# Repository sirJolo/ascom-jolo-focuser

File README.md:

ver 2.2 
==================
 - Driver local cache
 - Other fixes

ver 2.0 production
==================
 - EXT connector extended 
 - PCB redesigned a little and fixed
 - encoder support removed from Arduino sketch
 - 'Connection timeout for message #' bug fixed

ver 1.5 production
==================
Changelog:
 - encoder support removed
 - PWM stepper duty cycle control switched to Arduino native
 - Eagle project for PCB and reference schematic added (for fixed version wait for 1.6)
 - Reference solution uses L298 stepper driver and some of Arduino pins are now externally available for additional options. Driver implementation will be in 2.0

ver 1.4
==================
Changelog:
 - max focuser position now is 1,000,000
 - driver backslash control removed - noone uses it
 - buzzer turned off by default, can be turned on with BUZZER_ON flag
 - stepper now controlled with half step by default. Please change stepper speed (200%) and step size (50%) in driver settings
 - manual control now with two buttons that perform accelerated motion. Buttons connected to ENCODER_A_PIN and ENCODER_B_PIN
 - MANUAL_FOCUS_MODE added, default to 1 - control with button, NOT encoder
 - STEPPER_ACC increased to 2500
 - MANUAL_STEPPER_ACC for manual button control. Default is 600
 - STEPPER_PWM_FREQ changed to 1000Hz

ascom-jolo-focuser
==================
ASCOM absolute focuser developed using Arduino Nano board and Visual Studio 2008 for ASCOM driver. Uses DS1820 temperature sensor for temperature focus compensation and rotary encoder for manual focus change. Buzzer can be connected to indicate some user interactions, so there is no need to pay attention on any blinking LEDs. Communication with PC is performed over USB cable using Arduino Nano built in UART converter. RS commands set was chosen to implement ASCOM IFocus2 interface with minimum effort, so it is not compatibile with other focuser standards (like Robofocus) that have too much RS communication overhead.
Compiled microcontroller code is 18KB large, so it will not fit into boards with 16KB chip (like Arduino Nano version lower than 3.0). Code size can be shrinked by eliminating 3rd party libraries and making custom implementations.

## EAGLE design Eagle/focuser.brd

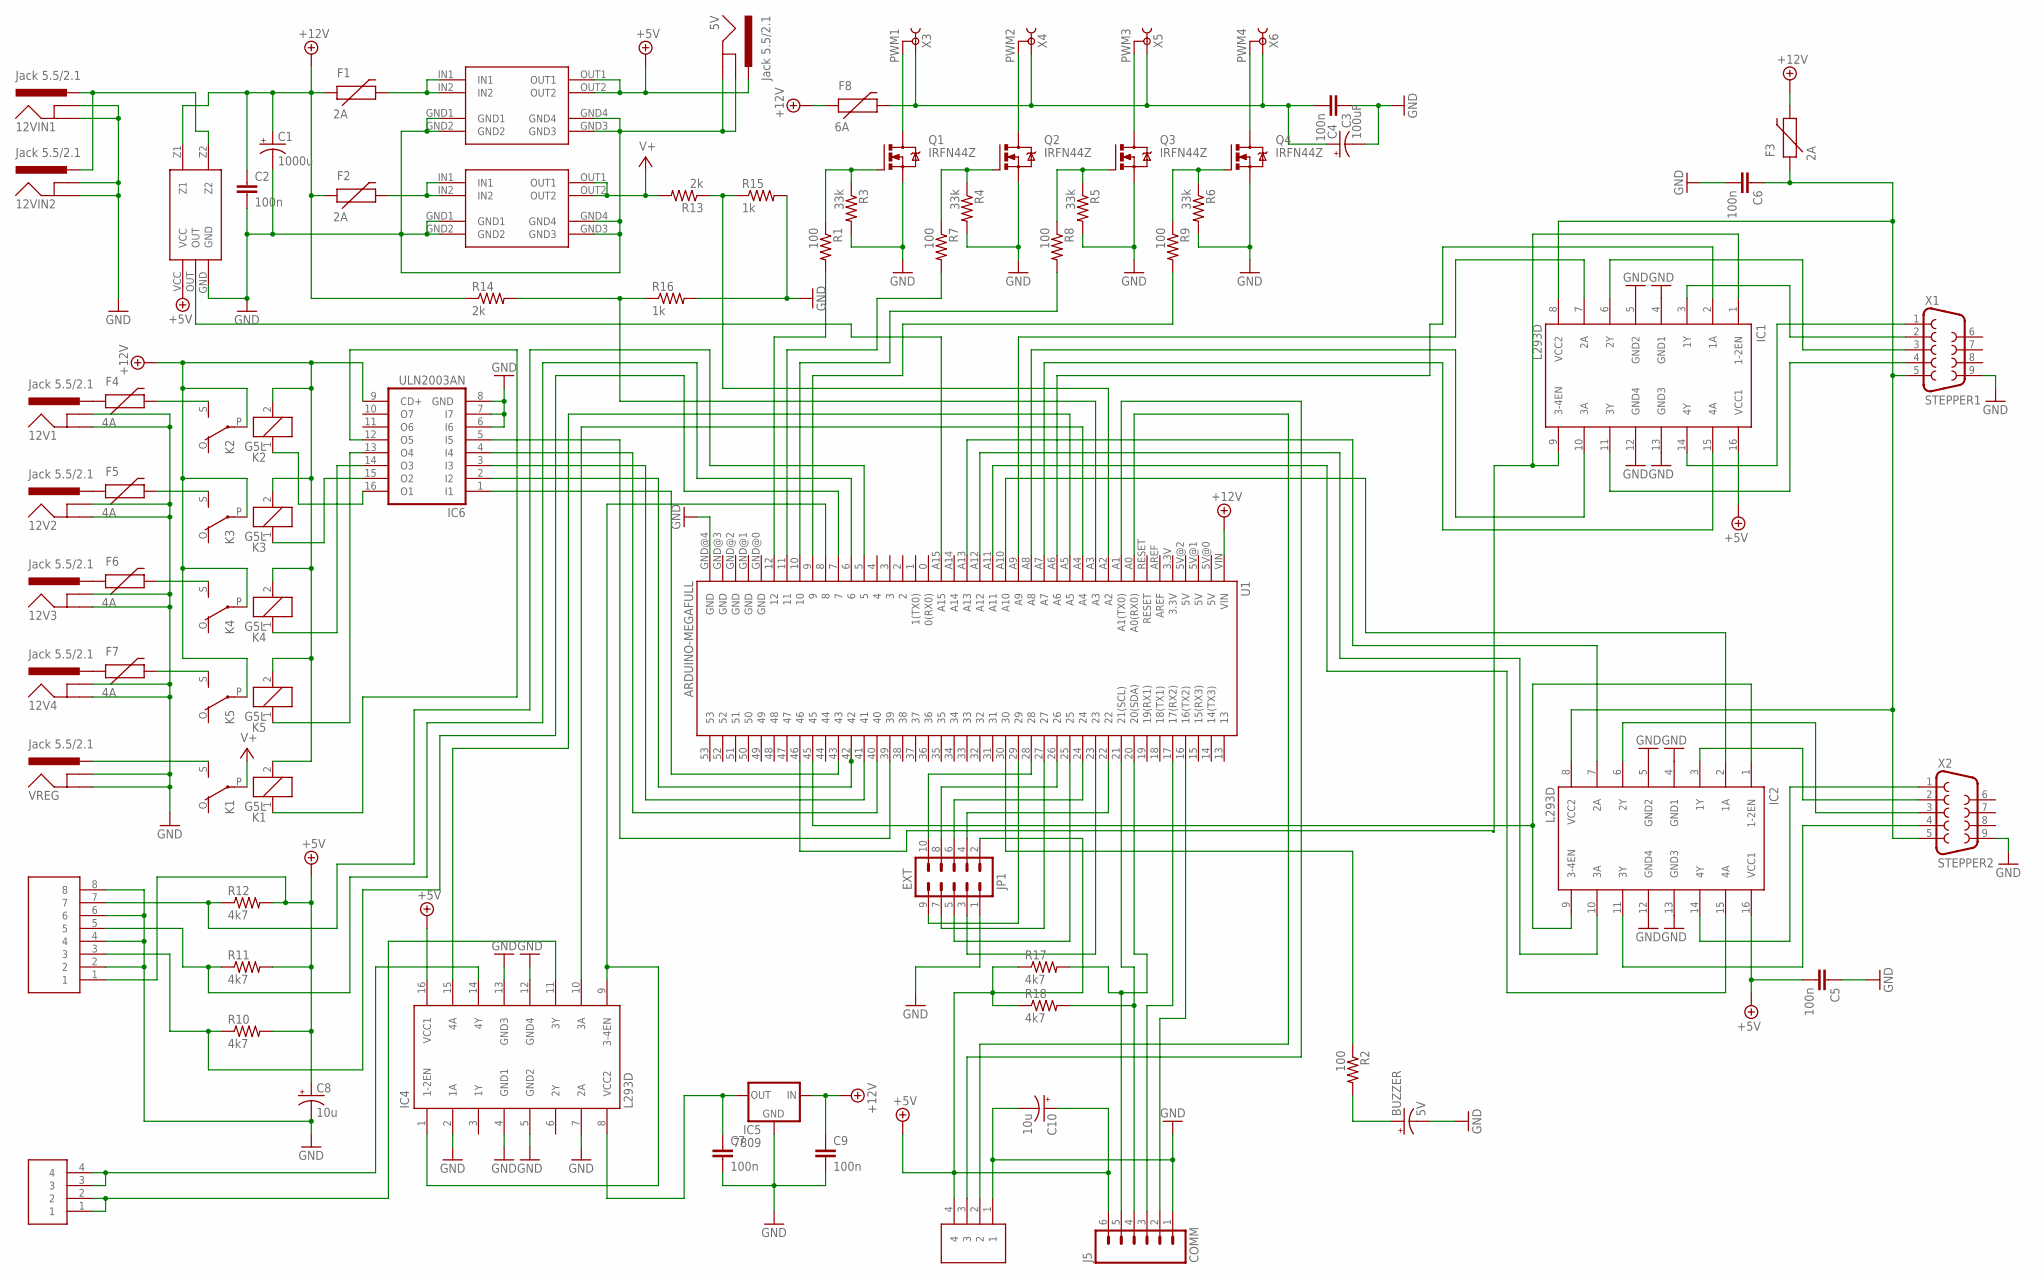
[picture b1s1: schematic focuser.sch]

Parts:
5V, 12V1, 12V2, 12V3, 12V4, 12VIN1, 12VIN2: Jack 5.5/2.1; POWER_JACK_PTH
BUZZER: 5V; CPOL-RADIAL-1000UF-25V
C1: 1000u; CPOL-RADIAL-1000UF-25V
C2, C3, C5, C6, C7, C9: 100n; CAP-PTH-5MM
C4: 100uF; CPOL-RADIAL-100UF-25V
C8, C10: 10u; CPOL-RADIAL-10UF-25V
F1, F2, F3: 2A; PTC
F4, F5, F6, F7: 4A; PTC
F8: 6A; PTC
IC1: L293D; DIL16
IC2, IC4: L293D; DIL16; MPN L293D
IC5: 7809; TO220-IGO
IC6: ULN2003AN; DIL16
J5: COMM; RJ11-6
JP1: EXT; AVR_ICSP
K1, K2, K3, K4, K5: G5L; G5LE
Q1, Q2, Q3, Q4: IRFN44Z; TO220BV
R1, R2, R7, R8, R9: 100; AXIAL-0.3
R3, R4, R5, R6: 33k; AXIAL-0.3
R10, R11, R12, R17, R18: 4k7; AXIAL-0.3
R13, R14: 2k; AXIAL-0.3
R15, R16: 1k; AXIAL-0.3
U1: ARDUINO-MEGAFULL; ARDUINO_MEGA
U$1, U$2: MP1584-BUCK; DCDC-1584
U$3: ASC712
U$4, U$5: RJ9
U$8: RJ45
VREG: Jack 5.5/2.1; POWER_JACK_PTH
X1: STEPPER1; DB9
X2: STEPPER2; DB9
X3: PWM1; TOBU3
X4: PWM2; TOBU3
X5: PWM3; TOBU3
X6: PWM4; TOBU3

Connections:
+5V: 5V.PWR, C5.2, C8.1 (+), C10.1 (+), IC1.16 (VCC1), IC2.16 (VCC1), IC4.16 (VCC1), J5.6, JP1.2, R10.P$2 (2), R11.P$2 (2), R12.P$2 (2), R17.P$1 (1), R18.P$1 (1), U$1.OUT1, U$1.OUT2, U$3.VCC, U$5.4, U$8.1
+12V: C1.1 (+), C2.1, C9.1, F1.P$1 (1), F2.P$1 (1), F3.P$2 (2), F8.P$1 (1), IC5.IN, IC6.9 (CD+), K1.2, K2.2, K2.P, K3.2, K3.P, K4.2, K4.P, K5.2, K5.P, R14.P$1 (1), U1.VIN, U$3.Z1
GND: 5V.GND, 5V.GNDBREAK, 12V1.GND, 12V1.GNDBREAK, 12V2.GND, 12V2.GNDBREAK, 12V3.GND, 12V3.GNDBREAK, 12V4.GND, 12V4.GNDBREAK, 12VIN1.GND, 12VIN1.GNDBREAK, 12VIN2.GND, 12VIN2.GNDBREAK, BUZZER.2 (-), C1.2 (-), C2.2, C3.1, C4.2 (-), C5.1, C6.2, C7.2, C8.2 (-), C9.2, C10.2 (-), IC1.4 (GND1), IC1.5 (GND2), IC1.12 (GND4), IC1.13 (GND3), IC2.4 (GND1), IC2.5 (GND2), IC2.12 (GND4), IC2.13 (GND3), IC4.2 (1A), IC4.4 (GND1), IC4.5 (GND2), IC4.7 (2A), IC4.12 (GND4), IC4.13 (GND3), IC5.GND, IC6.6 (I6), IC6.7 (I7), IC6.8 (GND), J5.1, JP1.1, Q1.S, Q2.S, Q3.S, Q4.S, R3.P$2 (2), R4.P$2 (2), R5.P$2 (2), R6.P$2 (2), R15.P$2 (2), R16.P$2 (2), U1.GND@4 (GND), U$1.GND1, U$1.GND2, U$1.GND3, U$1.GND4, U$2.GND1, U$2.GND2, U$2.GND3, U$2.GND4, U$3.GND, U$5.1, U$8.2, U$8.4, U$8.6, U$8.8, VREG.GND, VREG.GNDBREAK, X1.9, X2.9
unnamed: J5.4, R18.P$2 (2), U1.21 (21(SCL))
unnamed: J5.5, R17.P$2 (2), U1.20 (20(SDA))
unnamed: C7.1, IC4.8 (VCC2), IC5.OUT
unnamed: IC2.14 (4Y), X2.1
unnamed: IC1.3 (1Y), X1.2
unnamed: IC1.14 (4Y), X1.1
unnamed: IC1.11 (3Y), X1.4
unnamed: F4.P$2 (2), K2.S
unnamed: F5.P$2 (2), K3.S
unnamed: R9.P$2 (2), U1.9
unnamed: R8.P$2 (2), U1.10
unnamed: IC2.1 (1-2EN), IC2.9 (3-4EN), U1.45
unnamed: J5.3, U1.17 (17(RX2))
unnamed: R7.P$2 (2), U1.11
unnamed: IC2.6 (2Y), X2.3
unnamed: IC1.6 (2Y), X1.3
unnamed: J5.2, U1.16 (16(TX2))
unnamed: IC6.4 (I4), U1.40
unnamed: F6.P$2 (2), K4.S
unnamed: F7.P$2 (2), K5.S
unnamed: IC6.5 (I5), U1.39
unnamed: R13.P$1 (1), R15.P$1 (1), U1.A2
unnamed: IC4.15 (4A), U1.A5
unnamed: BUZZER.1 (+), R2.P$2 (2)
unnamed: IC6.2 (I2), U1.42
unnamed: 12VIN1.PWR, 12VIN2.PWR, U$3.Z2
unnamed: IC6.1 (I1), U1.43
unnamed: F2.P$2 (2), U$2.IN1, U$2.IN2
unnamed: IC6.3 (I3), U1.41
unnamed: IC4.1 (1-2EN), IC4.9 (3-4EN), U1.8
unnamed: IC4.10 (3A), U1.A4
unnamed: U1.A15, U$3.OUT
unnamed: IC1.7 (2A), U1.A9
unnamed: U1.A0 (A0(RX0)), U$5.2
unnamed: Q1.D, X3.2, X3.2@1 (2), X3.2@2 (2)
unnamed: Q2.D, X4.2, X4.2@1 (2), X4.2@2 (2)
unnamed: K1.S, VREG.PWR
unnamed: Q3.D, X5.2, X5.2@1 (2), X5.2@2 (2)
unnamed: Q4.G, R6.P$1 (1), R9.P$1 (1)
unnamed: Q3.G, R5.P$1 (1), R8.P$1 (1)
unnamed: Q2.G, R4.P$1 (1), R7.P$1 (1)
unnamed: Q1.G, R1.P$1 (1), R3.P$1 (1)
unnamed: 12V1.PWR, F4.P$1 (1)
unnamed: U1.A1 (A1(TX0)), U$5.3
unnamed: IC4.14 (4Y), U$4.3, U$4.4
unnamed: R2.P$1 (1), U1.30
unnamed: R14.P$2 (2), R16.P$1 (1), U1.A3
unnamed: IC1.10 (3A), U1.A8
unnamed: IC1.15 (4A), U1.A7
unnamed: IC1.2 (1A), U1.A6
unnamed: IC4.11 (3Y), U$4.1, U$4.2
unnamed: 12V2.PWR, F5.P$1 (1)
unnamed: JP1.4, U1.22
unnamed: IC6.14 (O3), K4.1
unnamed: IC6.13 (O4), K5.1
unnamed: IC6.15 (O2), K3.1
unnamed: IC6.16 (O1), K2.1
unnamed: C6.1, F3.P$1 (1), IC1.8 (VCC2), IC2.8 (VCC2), X1.5, X2.5
unnamed: R12.P$1 (1), U1.5, U$8.7
unnamed: 12V3.PWR, F6.P$1 (1)
unnamed: 12V4.PWR, F7.P$1 (1)
unnamed: JP1.3, U1.23
unnamed: IC6.12 (O5), K1.1
unnamed: Q4.D, X6.2, X6.2@1 (2), X6.2@2 (2)
unnamed: R11.P$1 (1), U1.6, U$8.5
unnamed: JP1.6, U1.24
unnamed: JP1.5, U1.25
unnamed: JP1.8, U1.26
unnamed: F1.P$2 (2), U$1.IN1, U$1.IN2
unnamed: JP1.7, U1.27
unnamed: R10.P$1 (1), U1.7, U$8.3
unnamed: JP1.10, U1.28
unnamed: IC2.11 (3Y), X2.4
unnamed: JP1.9, U1.29
unnamed: IC1.1 (1-2EN), IC1.9 (3-4EN), U1.46
unnamed: C3.2, C4.1 (+), F8.P$2 (2), X3.1, X4.1, X5.1, X6.1
unnamed: R1.P$2 (2), U1.12
unnamed: IC2.3 (1Y), X2.2
unnamed: IC2.7 (2A), U1.A13
unnamed: IC2.10 (3A), U1.A12
unnamed: IC2.15 (4A), U1.A11
unnamed: IC2.2 (1A), U1.A10
V+: K1.P, R13.P$2 (2), U$2.OUT1, U$2.OUT2

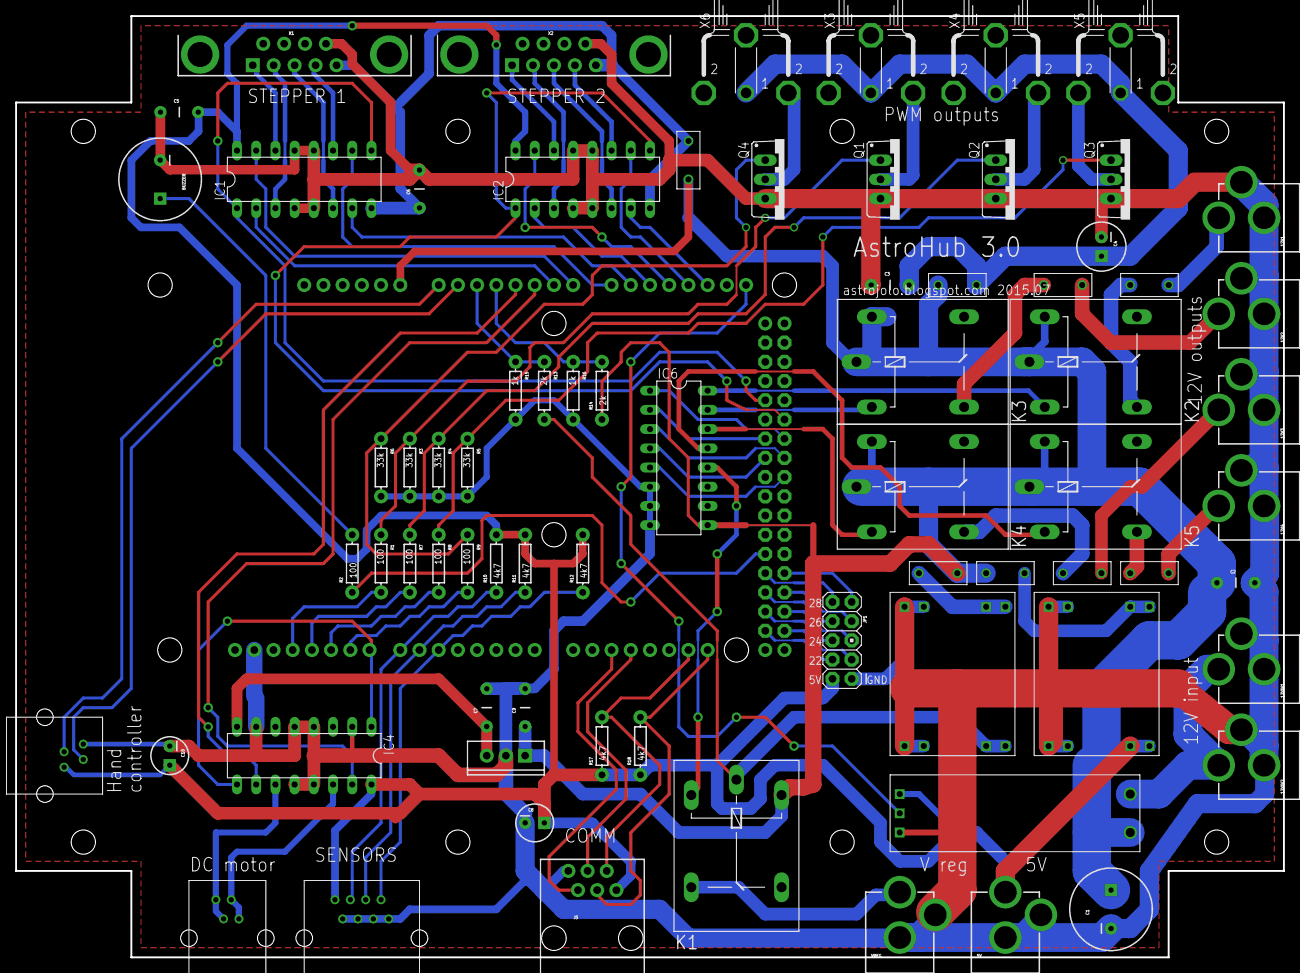
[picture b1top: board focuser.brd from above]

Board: 2 copper layers, 167.6 x 124.5 mm, 74 parts (1 on the bottom side), 86 nets.

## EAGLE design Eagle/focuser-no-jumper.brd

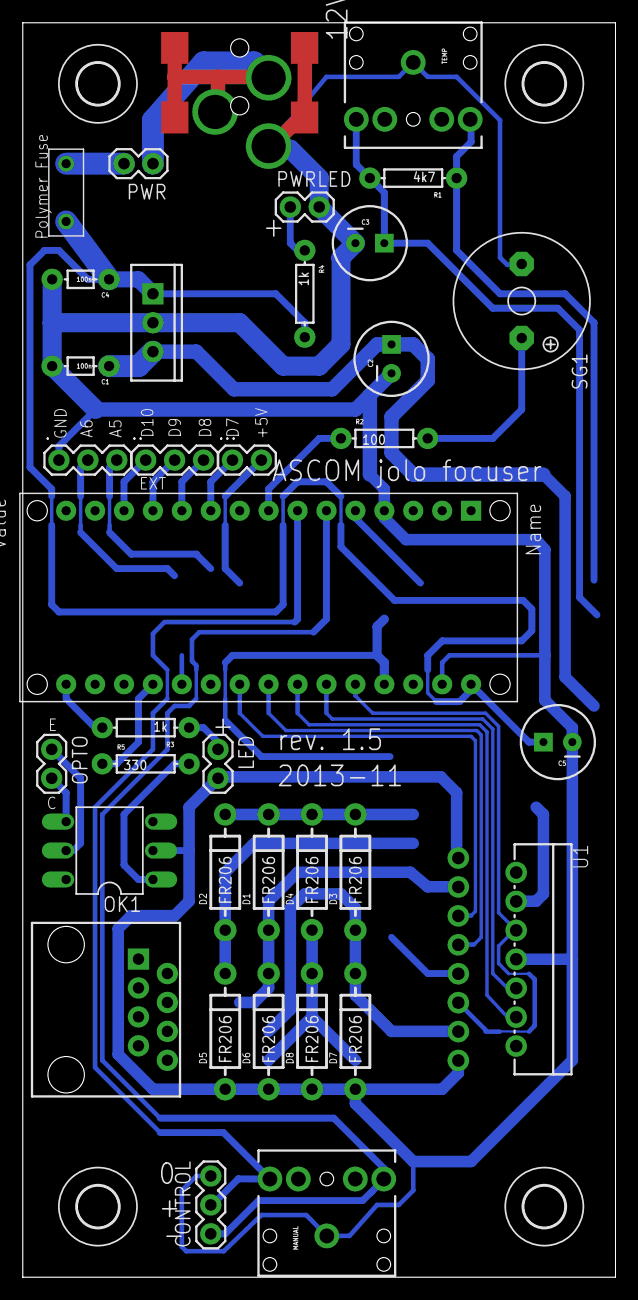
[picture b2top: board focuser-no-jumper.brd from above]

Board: 2 copper layers, 52.0 x 110.2 mm, 40 parts (0 on the bottom side), 33 nets.

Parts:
0.9A: PolyFuse; PTC
12V: Jack 5.5/2.1; POWER_JACK_COMBO
., ..: 1X03
...: 1X02
C1, C4: 100n; AXIAL-5MM
C2: 470u; CPOL-RADIAL-100UF-25V
C3: 10u; CPOL-RADIAL-100UF-25V
C5: 100u; CPOL-RADIAL-100UF-25V
CONTROL: J3; 1X03
D1, D2, D3, D4, D5, D6, D7, D8: FR206; DIODE-1N4001
IC1: 78xx; TO220-IGO
LED: 1X02
MANUAL: Jack 3.5mm; AUDIO-JACK
NANO: MMduino; PDIP-32
OK1: 4N35; DIL06
OPTO: 1X02
PWR: 1X02
PWRLED: 1X02
R1: 4k7; AXIAL-0.3
R2: 100; AXIAL-0.3
R3, R4: 1k; AXIAL-0.3
R5: 330; AXIAL-0.3
RJ45: Stepper; RJ45-8
SG1: Buzzer; F/QMBIII
TEMP: Jack 3.5mm; AUDIO-JACK
U1: L298; MULTIWATT15
U$2, U$3, U$4, U$5: 3,6

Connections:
+5: ....2, C3.1, NANO.+5V, R1.P$2, TEMP.5, U1.9
GND: 12V.POWER, ..1, C1.P$2, C2.2, C3.2, C4.P$2, C5.2, CONTROL.3, D5.A, D6.A, D7.A, D8.A, IC1.GND, LED.2, MANUAL.1, NANO.GND, NANO.GND1, OK1.2, PWRLED.2, SG1.-, TEMP.1, U1.1, U1.8, U1.15
unnamed: R2.P$2, SG1.+
unnamed: NANO.A0, U1.6, U1.11
unnamed: NANO.A4, U1.5
unnamed: NANO.A3, U1.7
unnamed: 0.9A.P$2, PWR.2
unnamed: ....1, NANO.D7
unnamed: 0.9A.P$1, C4.P$1, C5.1, IC1.IN, NANO.VIN, R4.P$2
unnamed: D4.A, D8.C, RJ45.7, RJ45.8, U1.14
unnamed: ..3, NANO.A5
unnamed: NANO.A1, U1.10
unnamed: D1.A, D6.C, RJ45.3, RJ45.4, U1.3
unnamed: NANO.A2, U1.12
unnamed: D2.A, D5.C, RJ45.1, RJ45.2, U1.2
unnamed: NANO.D2, R1.P$1, TEMP.2
unnamed: CONTROL.2, MANUAL.2, NANO.D4
unnamed: PWRLED.1, R4.P$1
unnamed: D3.A, D7.C, RJ45.5, RJ45.6, U1.13
unnamed: CONTROL.1, MANUAL.5, NANO.D3
unnamed: ..2, NANO.A6
unnamed: NANO.D13, R3.P$2
unnamed: LED.1, R3.P$1
unnamed: ...3, NANO.D8
unnamed: ...2, NANO.D9
unnamed: ...1, NANO.D10
unnamed: NANO.D5, R2.P$1
unnamed: NANO.A7, R5.P$1
unnamed: OK1.1, R5.P$2
unnamed: OK1.4, OPTO.2
unnamed: OK1.5, OPTO.1
VCC: 12V.GND@1, PWR.1
VCC2: C1.P$1, C2.1, D1.C, D2.C, D3.C, D4.C, IC1.OUT, U1.4

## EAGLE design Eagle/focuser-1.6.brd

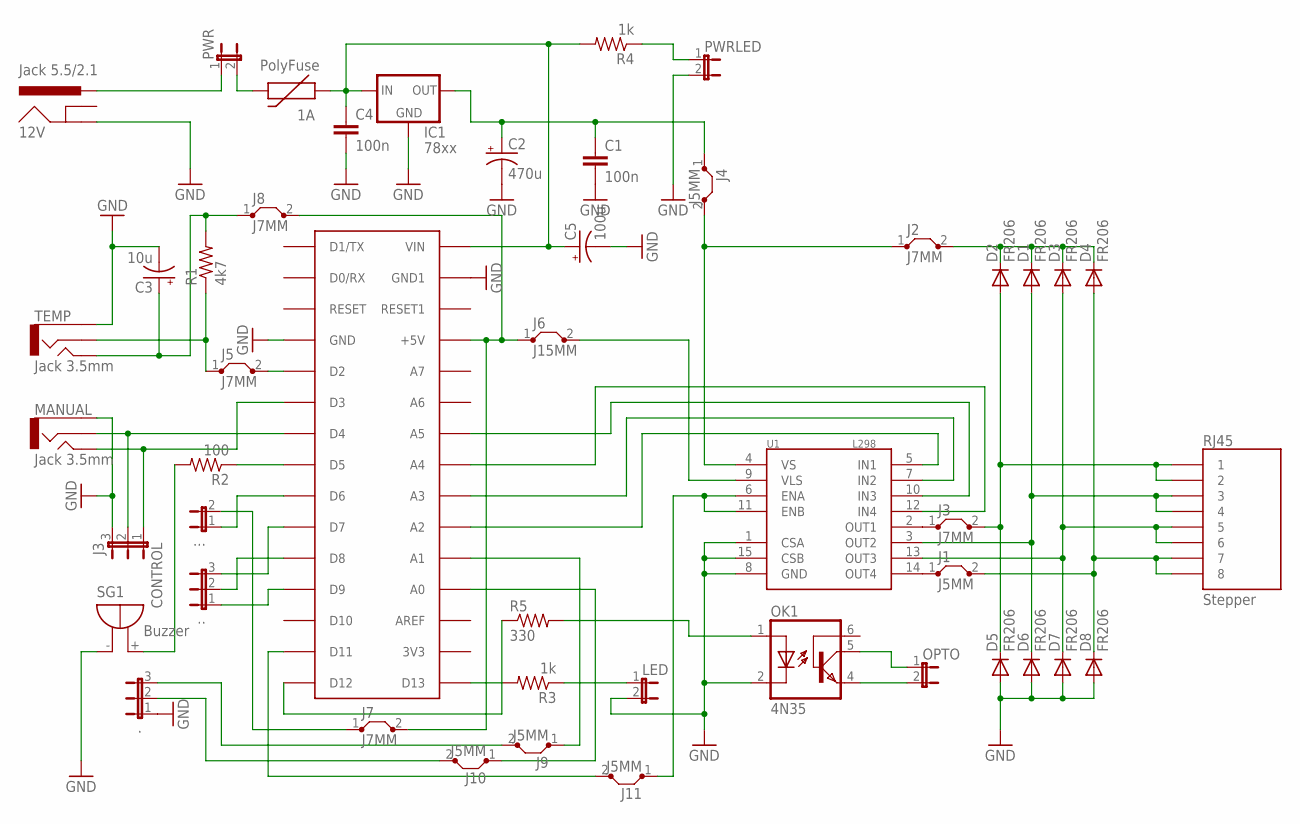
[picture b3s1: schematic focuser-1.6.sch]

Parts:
1A: PolyFuse; PTC
12V: Jack 5.5/2.1; POWER_JACK_COMBO
., ..: JUMPER-3PTH; 1X03
...: JUMPER-2PTH; 1X02
C1, C4: 100n; AXIAL-5MM
C2: 470u; CPOL-RADIAL-100UF-25V
C3: 10u; CPOL-RADIAL-100UF-25V
C5: 100u; CPOL-RADIAL-100UF-25V
CONTROL: J3; 1X03
D1, D2, D3, D4, D5, D6, D7, D8: FR206; DIODE-1N4001
IC1: 78xx; TO220-IGO
J1, J4, J9, J10, J11: J5MM; 05
J2, J3, J5, J7, J8: J7MM; 07
J6: J15MM; 15
LED: JUMPER-2PTH; 1X02
MANUAL: Jack 3.5mm; AUDIO-JACK
OK1: 4N35; DIL06
OPTO: JUMPER-2PTH; 1X02
PWR: JUMPER-2PTH; 1X02
PWRLED: JUMPER-2PTH; 1X02
R1: 4k7; AXIAL-0.3
R2: 100; AXIAL-0.3
R3, R4: 1k; AXIAL-0.3
R5: 330; AXIAL-0.3
RJ45: Stepper; RJ45-8
SG1: Buzzer; F/QMBIII
TEMP: Jack 3.5mm; AUDIO-JACK
U1: L298; MULTIWATT15
U$1: ARDUINONANO; PDIP-32

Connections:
+5: J6.1, J7.2, J8.2, U$1.+5V
GND: 12V.GND@1 (GND), ..1, C1.P$2 (2), C2.2 (-), C3.2 (-), C4.P$2 (2), C5.2 (-), CONTROL.3, D5.A, D6.A, D7.A, D8.A, IC1.GND, LED.2, MANUAL.1, OK1.2 (C), PWRLED.2, SG1.- (+), TEMP.1, U1.1 (CSA), U1.8 (GND), U1.15 (CSB), U$1.GND, U$1.GND1
unnamed: R2.P$2 (2), SG1.+ (-)
unnamed: J6.2, U1.9 (VLS)
unnamed: J11.2, U$1.D11
unnamed: U1.10 (IN3), U$1.A2 (A5)
unnamed: U1.7 (IN2), U$1.A4 (A3)
unnamed: ....2, J7.1
unnamed: 1A.P$2 (2), PWR.2
unnamed: ....1, U$1.D6
unnamed: 1A.P$1 (1), C4.P$1 (1), C5.1 (+), IC1.IN, R4.P$2 (2), U$1.VIN
unnamed: D4.A, D8.C, J1.2, RJ45.7, RJ45.8
unnamed: J1.1, U1.14 (OUT4)
unnamed: R5.P$1 (1), U$1.D12
unnamed: U1.12 (IN4), U$1.A3 (A4)
unnamed: D1.A, D6.C, RJ45.3, RJ45.4, U1.3 (OUT2)
unnamed: J11.1, U1.6 (ENA), U1.11 (ENB)
unnamed: D2.A, D5.C, J3.2, RJ45.1, RJ45.2
unnamed: J5.1, R1.P$1 (1), TEMP.2
unnamed: CONTROL.2, MANUAL.2, U$1.D4
unnamed: J5.2, U$1.D2
unnamed: PWRLED.1, R4.P$1 (1)
unnamed: D3.A, D7.C, RJ45.5, RJ45.6, U1.13 (OUT3)
unnamed: D1.C, D2.C, D3.C, D4.C, J2.2
unnamed: J3.1, U1.2 (OUT1)
unnamed: CONTROL.1, MANUAL.5, U$1.D3
unnamed: ..2, J10.2
unnamed: J2.1, J4.2, U1.4 (VS)
unnamed: R3.P$2 (2), U$1.D13
unnamed: LED.1, R3.P$1 (1)
unnamed: C3.1 (+), J8.1, R1.P$2 (2), TEMP.5
unnamed: ..3, J9.2
unnamed: ...3, U$1.D7
unnamed: ...2, U$1.D8
unnamed: ...1, U$1.D9
unnamed: R2.P$1 (1), U$1.D5
unnamed: J9.1, U$1.A6 (A1)
unnamed: OK1.1 (A), R5.P$2 (2)
unnamed: OK1.4 (EMI), OPTO.2
unnamed: OK1.5 (COL), OPTO.1
unnamed: 12V.POWER (PWR), PWR.1
unnamed: J10.1, U$1.A7 (A0)
unnamed: U1.5 (IN1), U$1.A5 (A2)
VCC2: C1.P$1 (1), C2.1 (+), IC1.OUT, J4.1

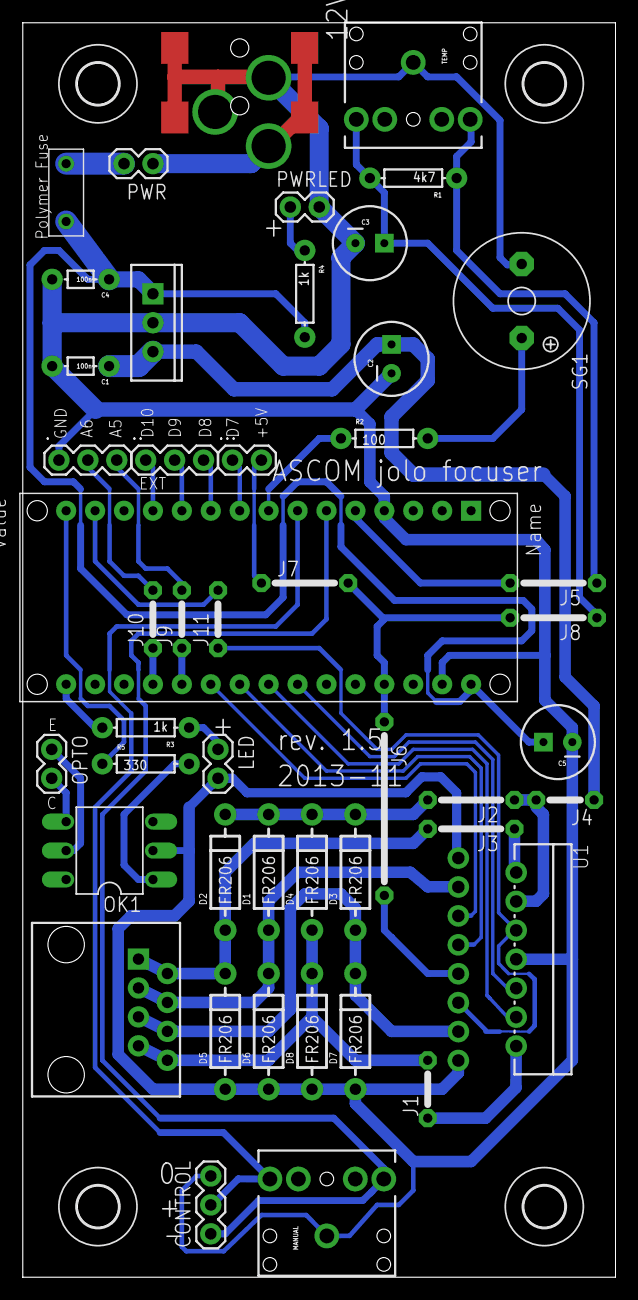
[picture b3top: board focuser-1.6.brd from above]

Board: 2 copper layers, 52.0 x 110.2 mm, 51 parts (0 on the bottom side), 44 nets.

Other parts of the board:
U$2, U$3, U$4, U$5: 3,6

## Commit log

2013-01-22 Initial Arduino sketch
2013-01-22 README.txt
2013-01-22 Structure changed
2013-01-22 Clean up
2013-01-22 arduino sketch update
2013-01-22 Stepper init speed fix.
2013-01-22 Sketch header added
2013-01-22 Pin reconfig
2013-01-23 Driver project init commit
2013-01-23 Temperature and backslash compensation
2013-01-23 Stepper lib added (issue #2)
2013-01-23 Non blocking temp read
2013-01-23 Non blocking stepper library
2013-01-24 Driver fixes
2013-01-24 minors
2013-01-24 Arduino clean up
2013-01-25 Issue 1
2013-01-26 Issue 6
2013-01-26 Stepper refactoring
2013-01-30 Async stepper lib
2013-01-31 misc
2013-02-03 New stepper lib
2013-02-03 Accel stepper back, bugfixes
2013-02-04 Driver set focuser position
2013-02-04 Some fixes
2013-02-06 Driver backslash, temp comp tested with device mock
2013-02-06 Driver installer
2013-02-06 Tested with Maxim DL
2013-02-06 Exception handling
2013-02-07 Old installer delete
2013-02-07 Old lib removed
2013-02-08 Driver setup dialog fixes
2013-02-08 Buzz control, high freq PWM lib
2013-02-12 Sketch work
2013-02-12 Some lost file
2013-02-16 Sketch RC1
2013-02-20 Focuser move limits
2013-02-20 Downloads folder
2013-02-26 RC ver 1.1
2013-09-23 ver 1.2
2013-11-08 ASCOM driver ver. 1.3
2013-11-08 Arduino ver. 1.3
2013-11-08 AccelStepper ver. 1.37 lib
2013-11-11 ver 1.4
2013-11-16 Production branch
2013-11-16 Encoder control removed. Pin config updated.
2013-11-18 Production PCB refactor
2013-11-18 2.0 VB changes
2013-11-20 Three components added for digital input, output and analog input
2013-11-22 OPTO simple and time control
2013-11-22 Fixes for 1.5
2013-11-28 OPTO schedule
2013-11-28 1.5 production refactor
2013-11-29 1.5 production drievr connection fix
2013-12-08 Final sketch 1.5
2013-12-10 Production final refactor
2013-12-10 Eagle project fix
2013-12-10 PCB fix for 1.6
2013-12-10 Readme
2013-12-16 Personalized ASCOM drivers
2014-03-12 Cleans
2014-03-19 LCD support
2014-04-07 Focuser 2.0
2014-04-08 Focuser 2.0 - PCB
2014-05-13 Arduino / Eagle updates
2014-05-17 Arduino update
2014-05-17 Arduino update / doc update
2014-05-17 Code clean up
2014-06-03 LCD, DHT updates
2014-06-04 Version 2.0 RC1
2014-06-09 Final 2.0
2014-06-11 Version 2.0 RC2
2014-06-11 Production 2.0 RC2
2014-06-21 Monitor window
2014-07-01 2.1 arduino working copy (LCD I2C DHT)
2014-07-08 2.1 arduino + ASCOM working copy
2014-07-09 2.1 arduino + ASCOM working copy + log + new communication format
2014-07-14 2.1 RC2
2014-07-14 2.1 RC3
2014-11-17 ASCOM driver return values caching added
2014-11-24 ASCOM driver ver. 2.2 - fixed: driver error when working from scripts due to not working sync lock
2014-11-25 PDF 2.2 update
2014-11-26 Sketch split and refactor.
2014-11-28 Sketch progressing...
2014-11-28 Config send over i2c
2014-12-02 Work continues... VB script update
2014-12-02 Muscle serial for testing (future for second ASCOM)
2014-12-04 JoloAccelStepper
2014-12-05 Stepper reverse
2014-12-10 Initial refactor
2014-12-10 Removed stored properties - no manual control anymore
2014-12-11 Driver refactor
2015-01-03 Utils fix
2015-01-03 README update
2015-01-13 JoloAccelStepper working
2015-02-27 no message
2015-04-22 Schematic update
2015-04-30 Mega code
2015-06-02 Z112A case part layout
2015-06-22 First PCB
2015-07-13 PCB fixes
2015-07-17 Pin changes
2015-07-21 Properties, buttons added.
2015-07-23 APO130 fixes
2015-07-23 2.5 adjusted
2015-08-18 New VB forms
2015-08-18 VB forms vertical
2015-08-19 VB forms almost completed...

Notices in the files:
parts and their libraries:
SparkFun: Licensing: CC v3.0 Share-Alike You are welcome to use this library for commercial purposes.
SparkFun-Connectors: Licensing: Creative Commons ShareAlike 4.0 International - https://creativecommons.org/licenses/by-sa/4.0
